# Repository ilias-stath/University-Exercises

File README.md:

This is a repository of exercises for varous courses of my University (University of Western Macedonia)

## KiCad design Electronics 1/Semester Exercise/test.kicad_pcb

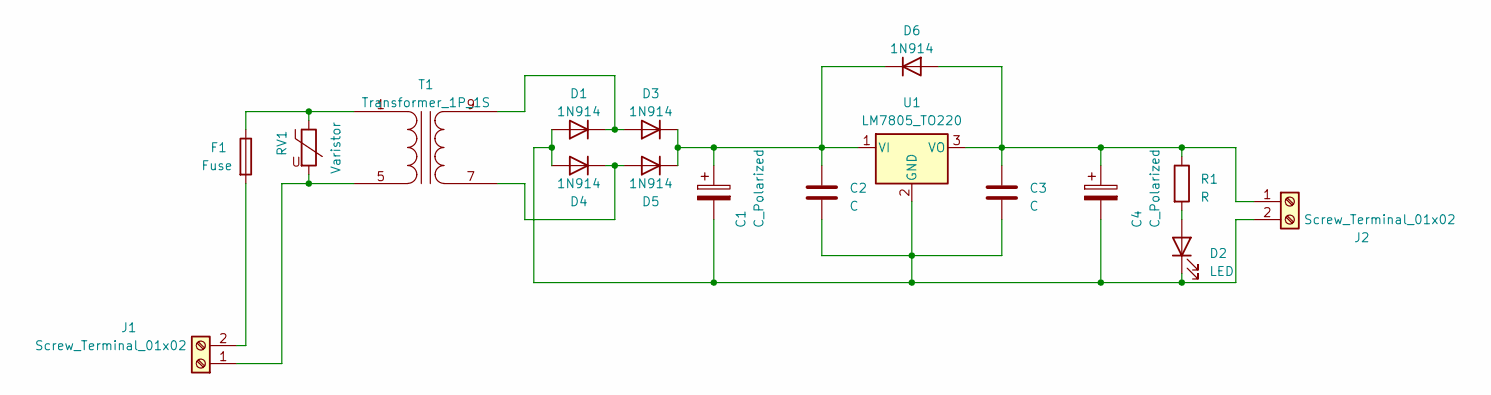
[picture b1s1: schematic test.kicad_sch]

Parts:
C1: C_Polarized; CP_Axial_L11.0mm_D8.0mm_P15.00mm_Horizontal
C2: C; C_Disc_D7.5mm_W5.0mm_P5.00mm
C3: C; C_Disc_D7.5mm_W2.5mm_P5.00mm
C4: C_Polarized; CP_Axial_L11.0mm_D5.0mm_P18.00mm_Horizontal
D1, D3, D4, D5: 1N914; D_DO-41_SOD81_P7.62mm_Horizontal
D2: LED; LED_D1.8mm_W1.8mm_H2.4mm_Horizontal_O1.27mm_Z1.6mm
D6: 1N914; D_DO-34_SOD68_P7.62mm_Horizontal
F1: Fuse; Fuse_0603_1608Metric
J1, J2: Screw_Terminal_01x02; TerminalBlock_bornier-2_P5.08mm
R1: R; R_Axial_DIN0204_L3.6mm_D1.6mm_P1.90mm_Vertical
RV1: Varistor; RV_Disc_D12mm_W3.9mm_P7.5mm
T1: Transformer_1P_1S; Transformer_Breve_TEZ-28x33
U1: LM7805_TO220; TO-220-3_Vertical

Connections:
unnamed: C1.2, C2.2, C3.2, C4.2, D1.2 (A), D2.1 (K), D4.2 (A), J2.2, U1.2 (GND)
unnamed: D1.1 (K), D3.2 (A), T1.9 (SB)
unnamed: D2.2 (A), R1.2
unnamed: C1.1, C2.1, D3.1 (K), D5.1 (K), D6.1 (K), U1.1 (VI)
unnamed: D4.1 (K), D5.2 (A), T1.7 (SA)
unnamed: C3.1, C4.1, D6.2 (A), J2.1, R1.1, U1.3 (VO)
unnamed: J1.1, RV1.2, T1.5 (AB)
unnamed: F1.2, J1.2
unnamed: F1.1, RV1.1, T1.1 (AA)

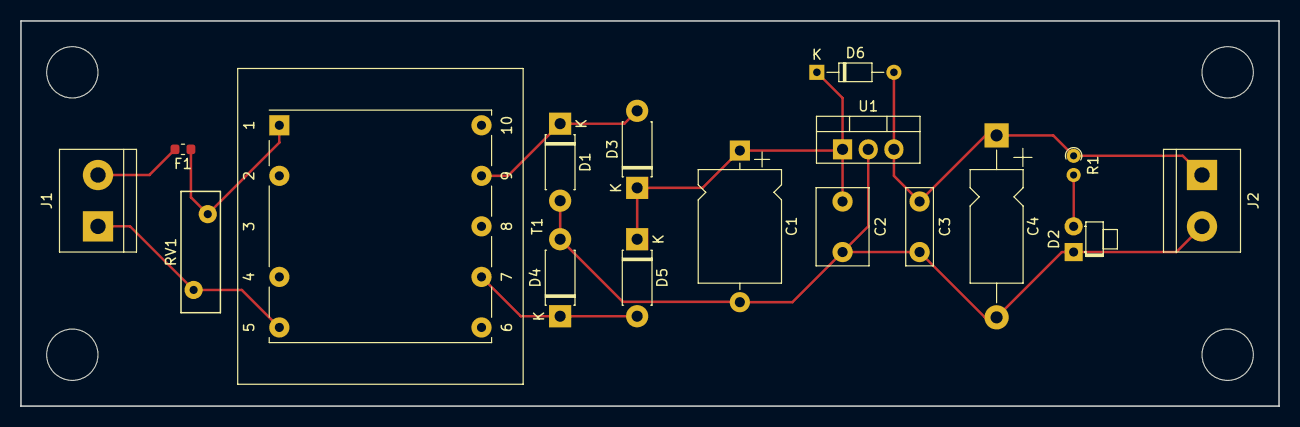
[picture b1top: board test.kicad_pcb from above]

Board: 2 copper layers, 124.5 x 38.1 mm, 17 parts (0 on the bottom side), 9 nets.

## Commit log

2024-10-12 Create τεστ
2024-10-12 Create sdf
2024-10-12 Create dghc
2024-10-12 Create ιτ
2024-10-12 Create yujgt
2024-10-12 Create dfgdg
2024-10-12 Create fth
2024-10-12 Create laboratory exercise 2
2024-10-12 Create Object Oriented Programming
2024-10-30 Rename sdf to blank
2024-10-30 Create blank
2024-10-30 Rename Άσκηση 1.pdf to Άσκηση 1(Επεξήγηση).pdf
2024-10-30 Rename Lab1.pdf to Lab1.pdf
2024-10-30 Changing names
2024-10-30 Chaning names
2024-10-30 Rename Σταθάκος_2017_1ηΕνότητα.pdf to 1η εργαστηριακή ενότητα_Κυκλώματα RC και CR.pdf
2024-10-30 Update and rename Suggested topics.docx to My Topic
2024-10-30 Rename My Topic to My Topic.doc
2024-10-30 Rename My Topic.doc to My Topic.docx
2024-10-30 Changing dir
2025-08-29 Create t
2025-12-04 Create LICENSE
